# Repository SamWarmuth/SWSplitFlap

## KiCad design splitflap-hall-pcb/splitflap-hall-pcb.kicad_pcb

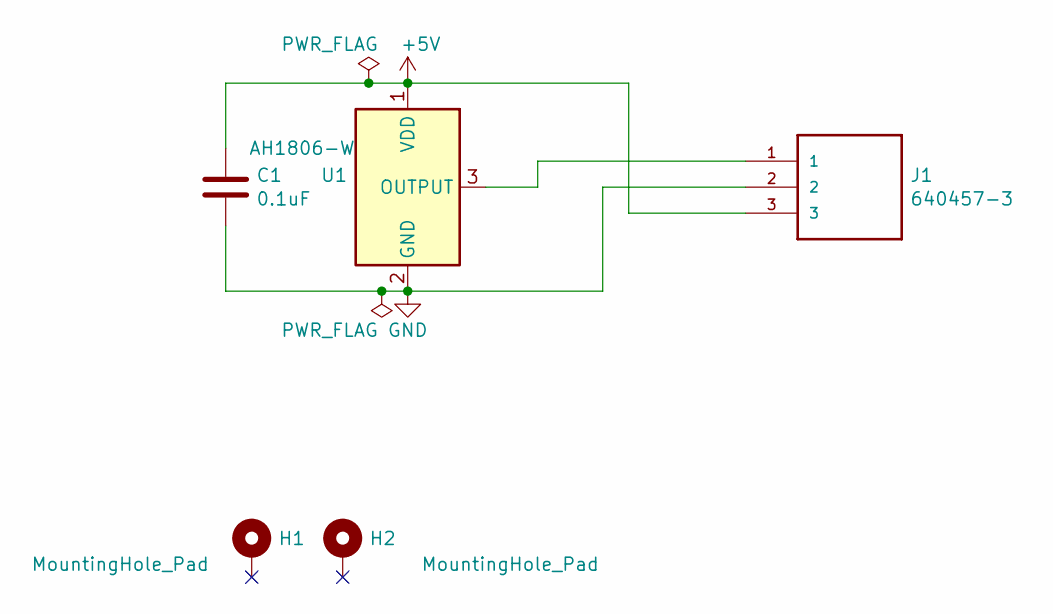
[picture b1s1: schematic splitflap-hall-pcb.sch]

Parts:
C1: 0.1uF; C_0603_1608Metric
H1, H2: MountingHole_Pad; MountingHole_3.2mm_M3_Pad
J1: 640457-3; TE_640457-3
U1: AH1806-W; SC-59

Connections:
+5V: C1.1, J1.3, U1.1 (VDD)
GND: C1.2, J1.2, U1.2 (GND)
unnamed: J1.1, U1.3 (OUTPUT)

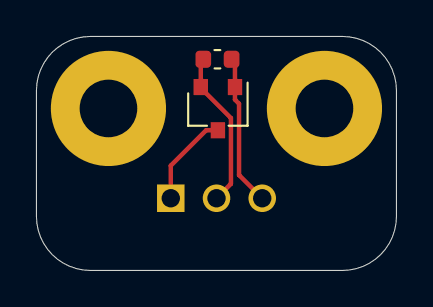
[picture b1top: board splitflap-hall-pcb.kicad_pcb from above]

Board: 2 copper layers, 20.0 x 13.0 mm, 5 parts (1 on the bottom side), 3 nets.

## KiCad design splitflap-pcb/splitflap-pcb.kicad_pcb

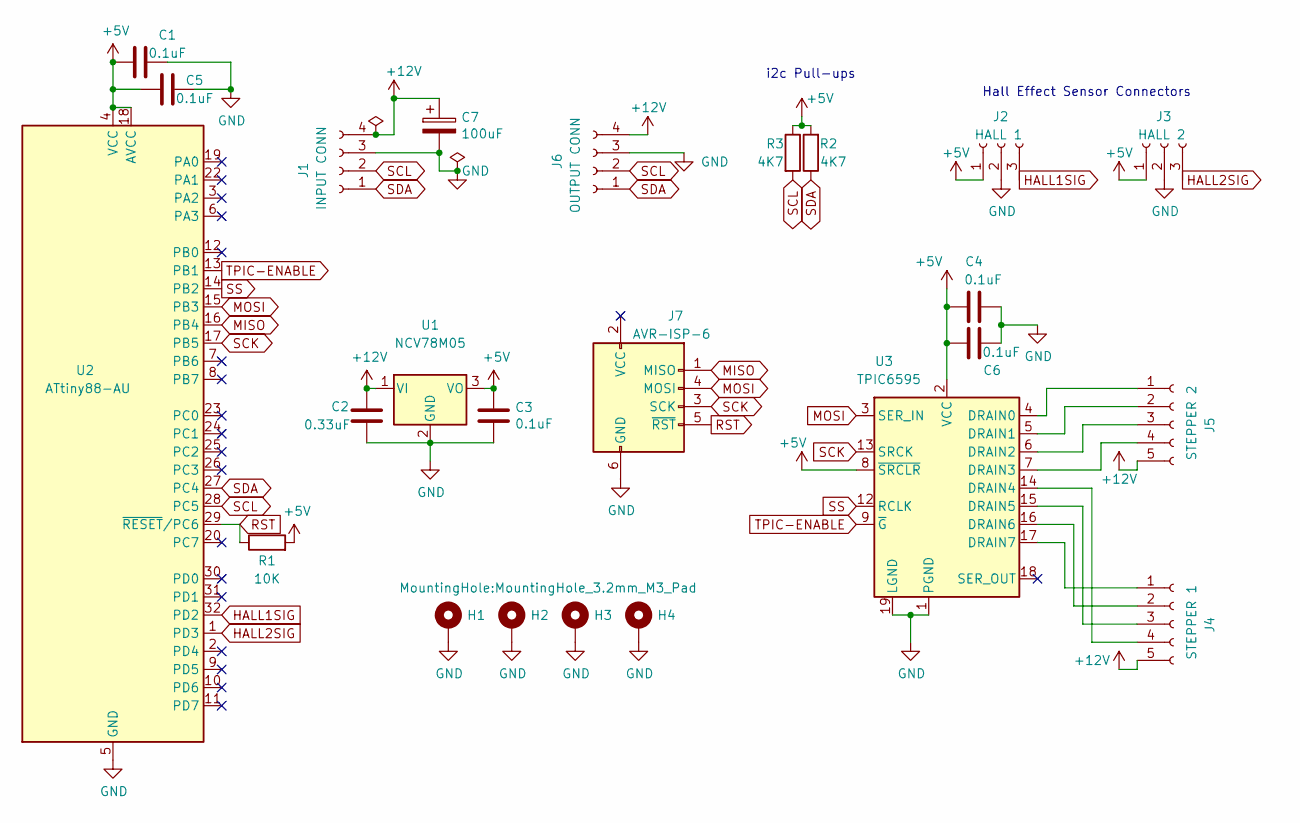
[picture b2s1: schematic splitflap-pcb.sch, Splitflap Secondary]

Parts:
C1, C3, C4, C5, C6: 0.1uF; C_0603_1608Metric
C2: 0.33uF; C_0603_1608Metric
C7: 100uF; CP_Radial_D6.3mm_P2.50mm
H1, H2, H3, H4: MountingHole_Pad; MountingHole_3.2mm_M3_Pad
J1: INPUT CONN; TE_640456-4
J2: HALL 1; TE_640456-3
J3: HALL 2; TE_640456-3
J4: STEPPER 1; JST_XH_B5B-XH-A_1x05_P2.50mm_Vertical
J5: STEPPER 2; JST_XH_B5B-XH-A_1x05_P2.50mm_Vertical
J6: OUTPUT CONN; TE_640456-4
J7: AVR-ISP-6; PinHeader_2x03_P2.54mm_Vertical
R1: 10K; R_0603_1608Metric
R2, R3: 4K7; R_0603_1608Metric
U1: NCV78M05; TO-252-2
U2: ATtiny88-AU; TQFP-32_7x7mm_P0.8mm
U3: TPIC6595; SOIC-20W_7.5x12.8mm_P1.27mm

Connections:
+5V: C1.2, C3.1, C4.1, C5.2, C6.1, J2.1, J3.1, R1.2, R2.2, R3.1, U1.3 (VO), U2.4 (VCC), U2.18 (AVCC), U3.2 (VCC), U3.8 (~SRCLR)
+12V: C2.1, C7.1, J1.4, J4.5, J5.5, J6.4, U1.1 (VI)
GND: C1.1, C2.2, C3.2, C4.2, C5.1, C6.2, C7.2, H1.1, H2.1, H3.1, H4.1, J1.3, J2.2, J3.2, J6.3, J7.6 (GND), U1.2 (GND), U2.5 (GND), U2.21 (GND), U3.1 (PGND), U3.10 (PGND), U3.11 (PGND), U3.19 (LGND), U3.20 (PGND)
HALL1SIG: J2.3, U2.32 (PD2)
HALL2SIG: J3.3, U2.1 (PD3)
MISO: J7.1 (MISO), U2.16 (PB4)
MOSI: J7.4 (MOSI), U2.15 (PB3), U3.3 (SER_IN)
unnamed: J4.1, U3.17 (DRAIN7)
unnamed: J4.2, U3.16 (DRAIN6)
unnamed: J4.3, U3.15 (DRAIN5)
unnamed: J4.4, U3.14 (DRAIN4)
unnamed: J5.1, U3.4 (DRAIN0)
unnamed: J5.2, U3.5 (DRAIN1)
unnamed: J5.3, U3.6 (DRAIN2)
unnamed: J5.4, U3.7 (DRAIN3)
RST: J7.5 (~RST), R1.1, U2.29 (~RESET~/PC6)
SCK: J7.3 (SCK), U2.17 (PB5), U3.13 (SRCK)
SCL: J1.2, J6.2, R3.2, U2.28 (PC5)
SDA: J1.1, J6.1, R2.1, U2.27 (PC4)
SS: U2.14 (PB2), U3.12 (RCLK)
TPIC-ENABLE: U2.13 (PB1), U3.9 (~G)

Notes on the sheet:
i2c Pull-ups
Hall Effect Sensor Connectors

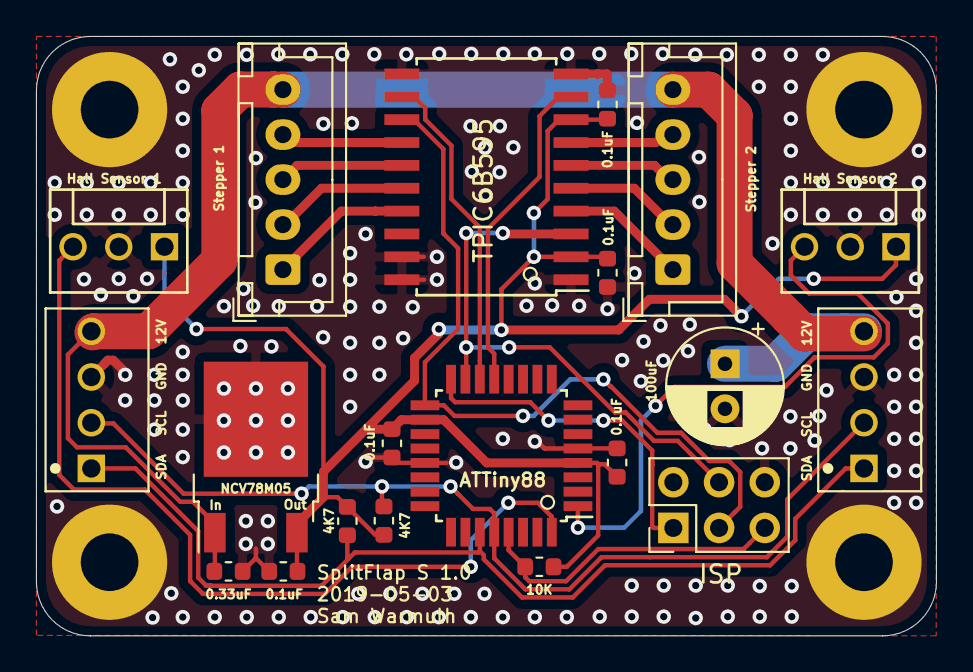
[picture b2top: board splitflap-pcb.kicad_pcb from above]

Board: 2 copper layers, 50.0 x 33.3 mm, 24 parts (0 on the bottom side), 21 nets.

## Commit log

2019-04-10 Something is broken. Should have gotten this into git earlier
2019-04-10 Woo! Actually figured out which poles are which
2019-04-10 Tweak hall position to make top flap farther forward
2019-04-16 Update pin notes, getting ready to switch to attiny88
2019-04-16 Working! Rearrange files
2019-04-17 Working esp32 i2c
2019-04-19 Save work from yesterdaty
2019-04-29 Add pcb files
2019-04-29 Redesign PCB, connectors are too big
2019-04-29 Getting ready to global delete tracks
2019-04-29 Actually the correct footprints
2019-04-29 placed components
2019-04-29 Add dsn
2019-04-29 Wired
2019-04-30 Closer, working on stitching
2019-04-30 new netlist
2019-04-30 new files
2019-04-30 More
2019-05-01 Tweaks
2019-05-02 just before panelizing
2019-05-02 Update config
2019-05-02 update python path
2019-05-02 Giving up on panelizing for now
2019-05-03 v10, almost ready to order
2019-05-03 Ordered panelized v1.0
2019-05-05 rename screenshots folder to play nice on windows
2019-05-06 Cleanup
2019-05-07 rounded corners
2019-05-08 Add notes
2019-05-08 Add images
2019-05-11 add more notes
2019-05-13 add hall pcb
2019-05-13 More notes, small updates
2019-05-13 Hall PCB
2019-05-13 Rotate SFH 90 degrees
2019-05-13 Un-panelize
2019-05-13 add gerber
2019-05-13 Pull raw gerber files
